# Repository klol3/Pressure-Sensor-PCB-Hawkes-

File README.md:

# Pressure-Sensor-PCB-Hawkes-
Electrical schematics and code for the pressure sensor PCB

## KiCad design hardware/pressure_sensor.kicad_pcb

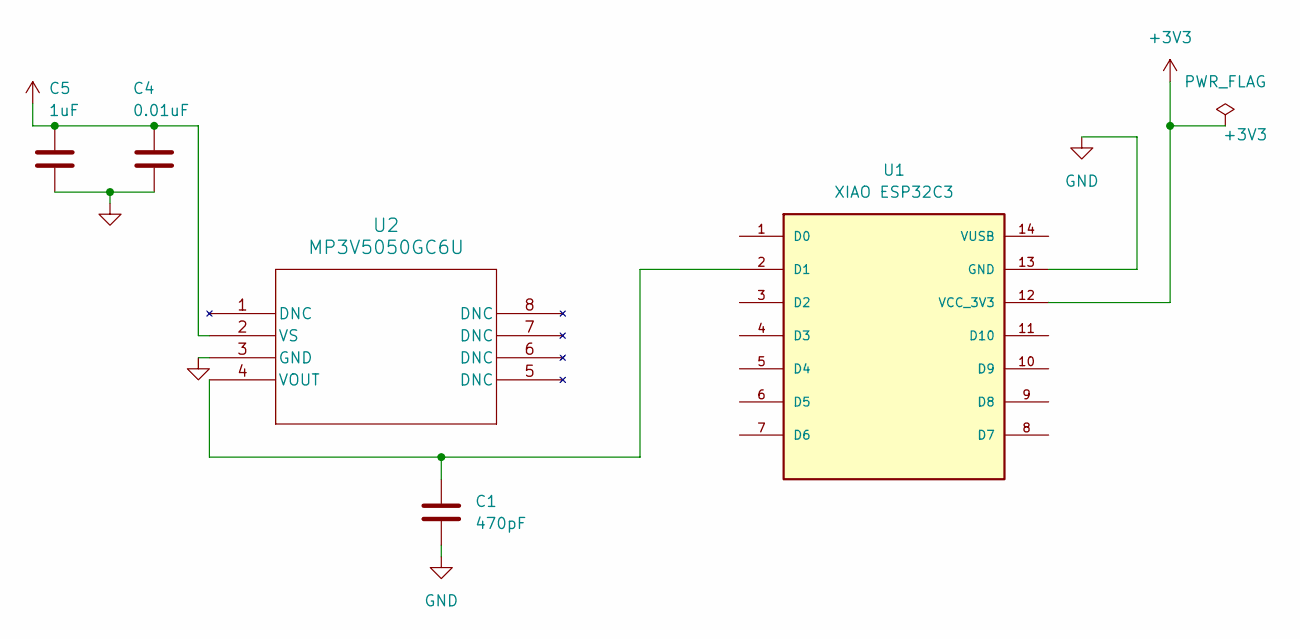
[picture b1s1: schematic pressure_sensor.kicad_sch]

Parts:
C1: 470pF; C_0805_2012Metric_Pad1.18x1.45mm_HandSolder
C4: 0.01uF; C_0805_2012Metric_Pad1.18x1.45mm_HandSolder
C5: 1uF; C_0805_2012Metric_Pad1.18x1.45mm_HandSolder
U1: XIAO ESP32C3; MCU_Seeed_ESP32C3
U2: MP3V5050GC6U; Pressure_Sensor_MP3v5050GC6U

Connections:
+3V3: C4.1, C5.1, U1.12 (VCC_3V3), U2.2 (VS)
GND: C1.2, C4.2, C5.2, U1.13 (GND), U2.3 (GND)
unnamed: C1.1, U1.2 (D1), U2.4 (VOUT)

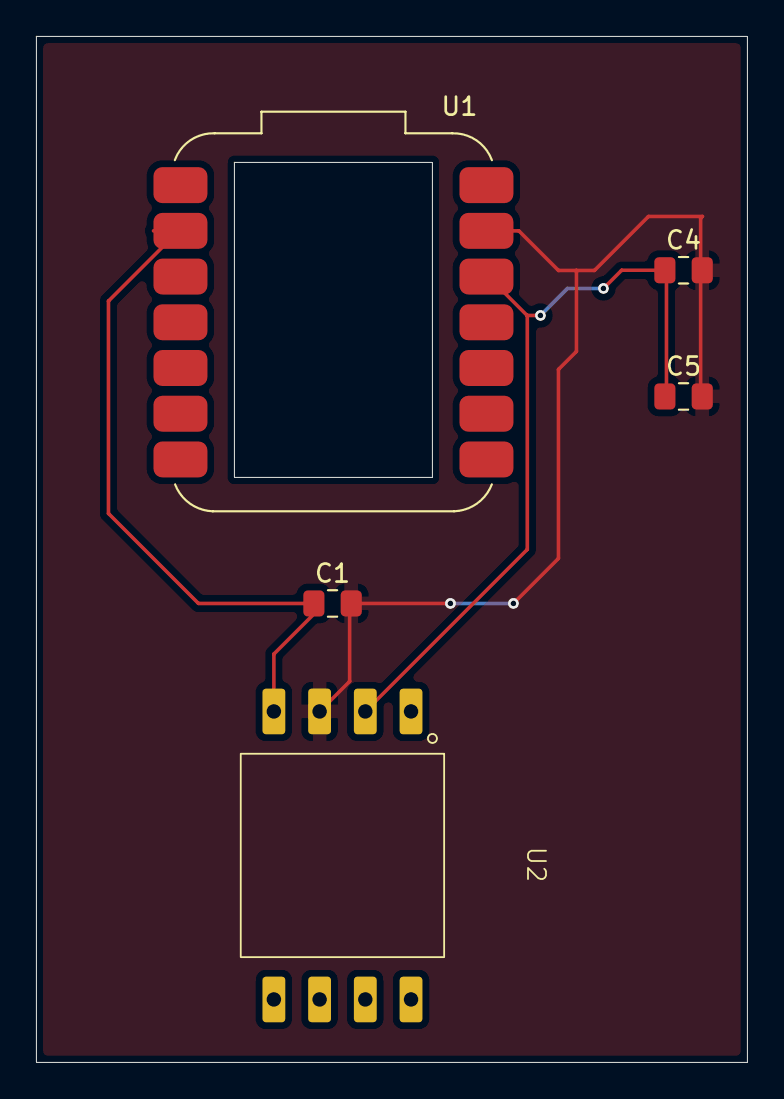
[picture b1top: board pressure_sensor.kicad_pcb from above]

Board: 2 copper layers, 39.5 x 57.0 mm, 5 parts (0 on the bottom side), 3 nets.

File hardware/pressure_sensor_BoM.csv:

"Id";"Designator";"Footprint";"Quantity";"Designation";"Supplier and ref";
1;"C1";"C_0805_2012Metric_Pad1.18x1.45mm_HandSolder";1;"470µF";;;
2;"C4";"C_0805_2012Metric_Pad1.18x1.45mm_HandSolder";1;"0.01uF";;;
3;"C5";"C_0805_2012Metric_Pad1.18x1.45mm_HandSolder";1;"1uF";;;
4;"U1";"MCU_Seeed_ESP32C3";1;"XIAO ESP32C3";;;
5;"U2";"Pressure_Sensor_MP3v5050GC6U";1;"MP3V5050GC6U";;;
